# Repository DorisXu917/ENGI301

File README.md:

<h1> ENGI301
Repository for ENGI301 course work

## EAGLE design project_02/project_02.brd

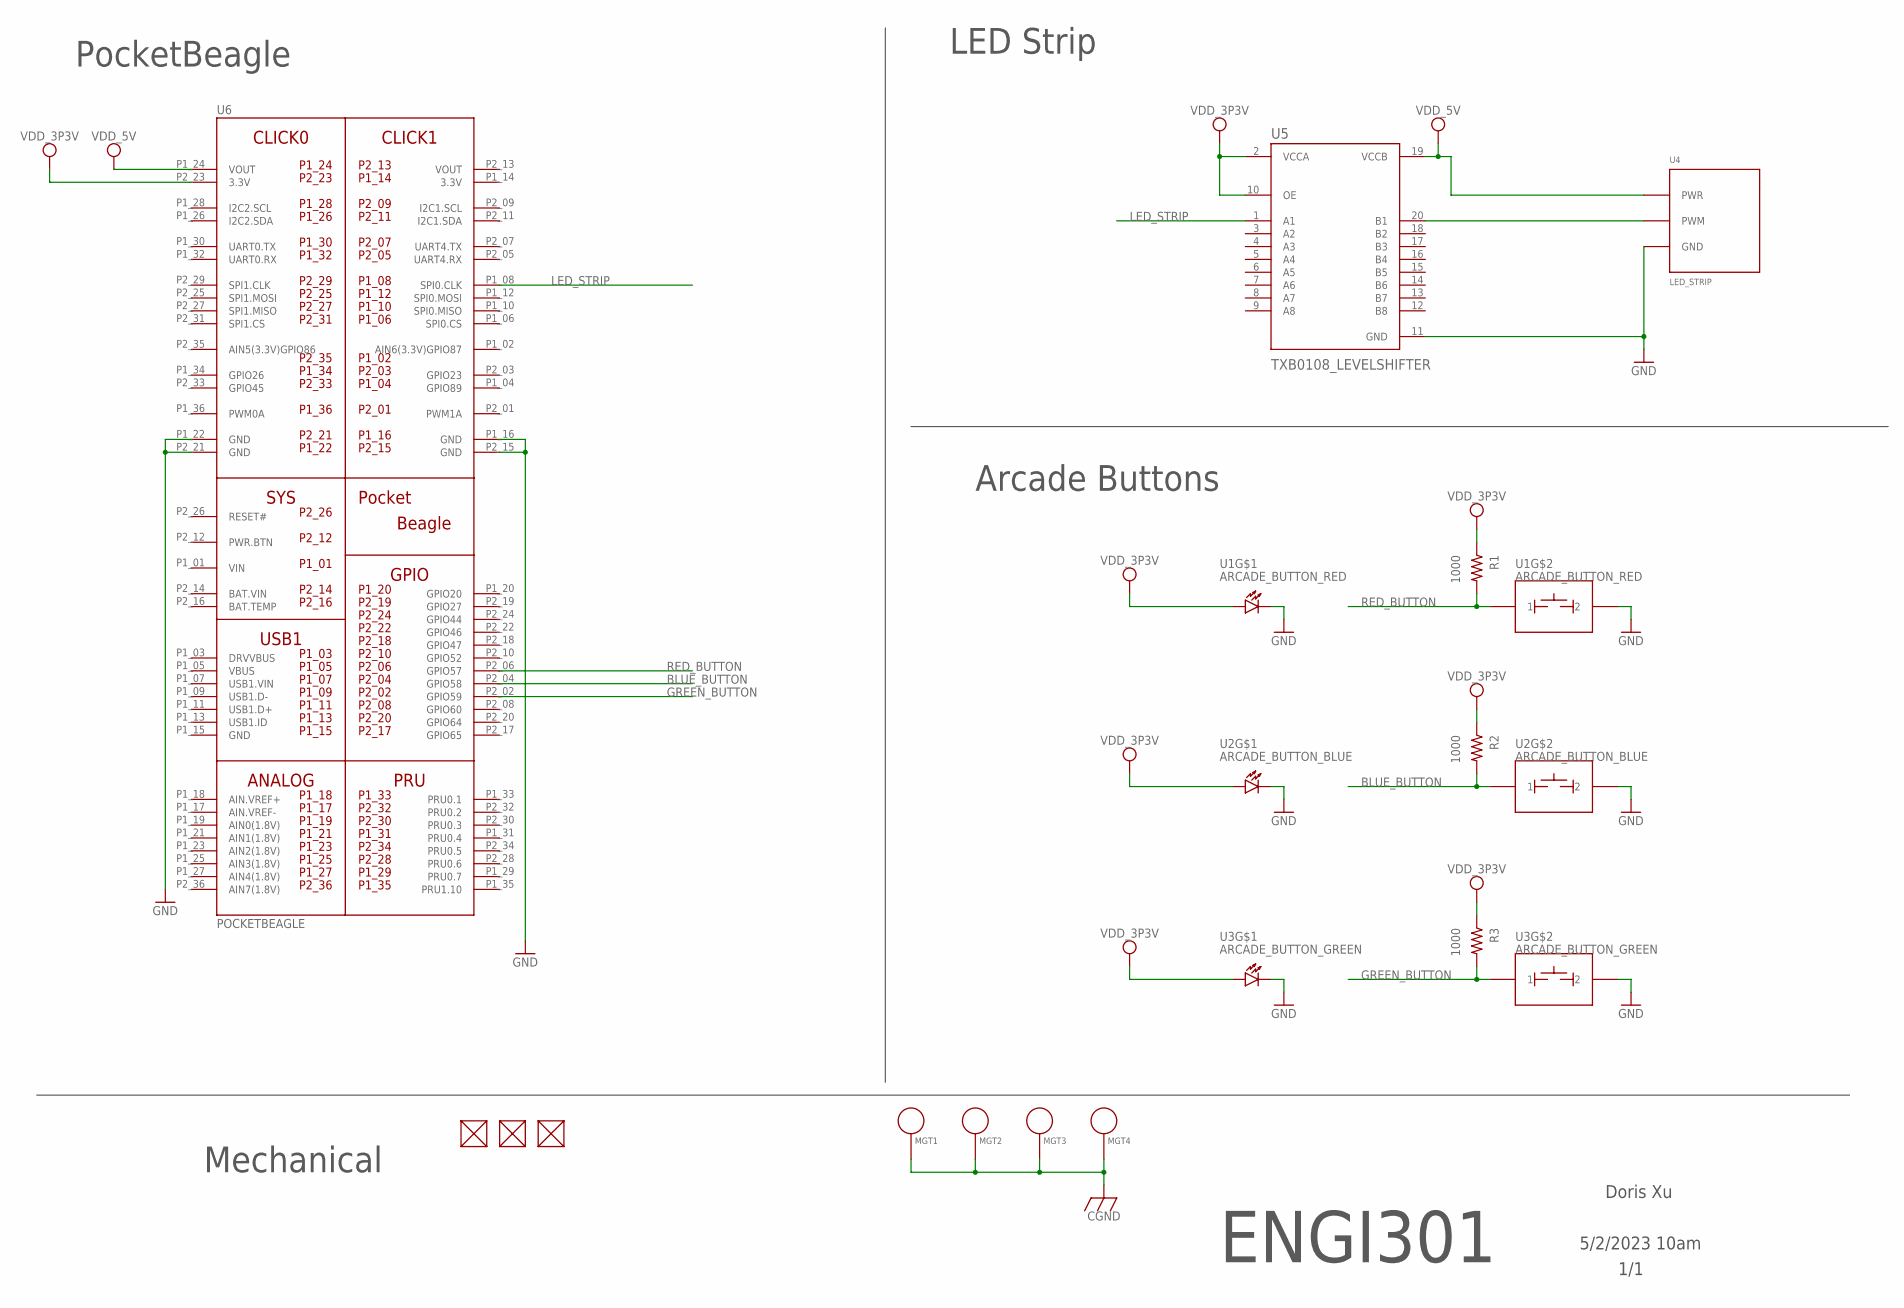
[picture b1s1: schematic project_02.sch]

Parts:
FUD1, FUD2, FUD3: FIDUCIAL; FIDUCIAL_40MIL
MGT1, MGT2, MGT3, MGT4: MOUNTING_HOLE
R1, R2, R3: 1000; R1206
U1: ARCADE_BUTTON_RED; LED_BUTTON
U2: ARCADE_BUTTON_BLUE; LED_BUTTON
U3: ARCADE_BUTTON_GREEN; LED_BUTTON
U4: LED_STRIP
U5: TXB0108_LEVELSHIFTER; SOP65P640X120-20N
U6: POCKETBEAGLE

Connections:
3.3V: U6.P1_14 (3.3V)
BAT.VIN: U6.P2_14 (BAT.VIN)
BLUE_BUTTON: R2.2, U2.BUTTON_1 (1), U6.P2_04 (GPIO58)
CGND: MGT1.P$1, MGT2.P$1, MGT3.P$1, MGT4.P$1
GND: U1.BUTTON_2 (2), U1.CATHODE, U2.BUTTON_2 (2), U2.CATHODE, U3.BUTTON_2 (2), U3.CATHODE, U4.GND, U5.11 (GND), U6.P1_16 (GND), U6.P1_22 (GND), U6.P2_15 (GND), U6.P2_21 (GND)
GREEN_BUTTON: R3.2, U3.BUTTON_1 (1), U6.P2_02 (GPIO59)
LED_SIGNAL: U4.SIG (PWM), U5.20 (B1)
LED_STRIP: U5.1 (A1), U6.P1_08 (SPI0.CLK)
RED_BUTTON: R1.2, U1.BUTTON_1 (1), U6.P2_06 (GPIO57)
VDD_3P3V: R1.1, R2.1, R3.1, U1.ANODE, U2.ANODE, U3.ANODE, U5.2 (VCCA), U5.10 (OE), U6.P2_23 (3.3V)
VDD_5V: U4.PWR, U5.19 (VCCB), U6.P1_24 (VOUT)
VIN: U6.P1_01 (VIN)
VOUT: U6.P2_13 (VOUT)

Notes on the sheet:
PocketBeagle
Mechanical
Arcade Buttons
LED Strip
ENGI301
Doris Xu
1/1
5/2/2023 10am

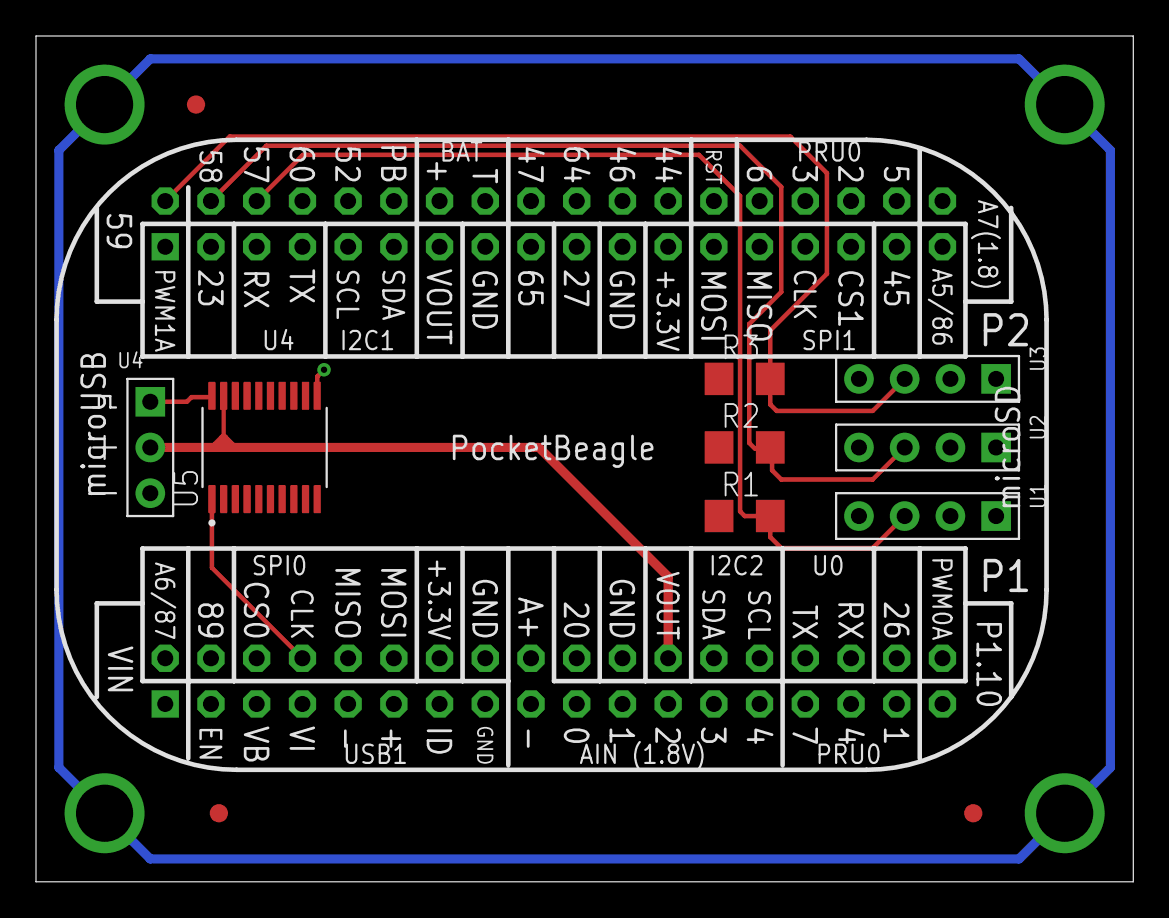
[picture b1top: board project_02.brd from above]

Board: 2 copper layers, 61.0 x 47.0 mm, 16 parts (0 on the bottom side), 9 nets.

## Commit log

2023-01-31 Update README.md
    Edited README file
2023-02-12 added python files for hw4
2023-02-12 added new files for hw4
2023-02-12 edited simple_calc to make the left and right shift functions work with int
2023-02-12 edited the button.py file to complete the coding exercise in hw4
2023-02-12 added comments and documentation to the blink LED file
    added new files
2023-03-30 Add files via upload
    backed up project code
2023-05-03 added project2
2023-05-03 Add files via upload
    added project 2 files
2023-05-03 Add files via upload
    added project 2 pictures
